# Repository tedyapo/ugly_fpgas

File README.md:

# ugly_fpgas
Breakout PCBs for ugly-style prototyping with small FPGAs

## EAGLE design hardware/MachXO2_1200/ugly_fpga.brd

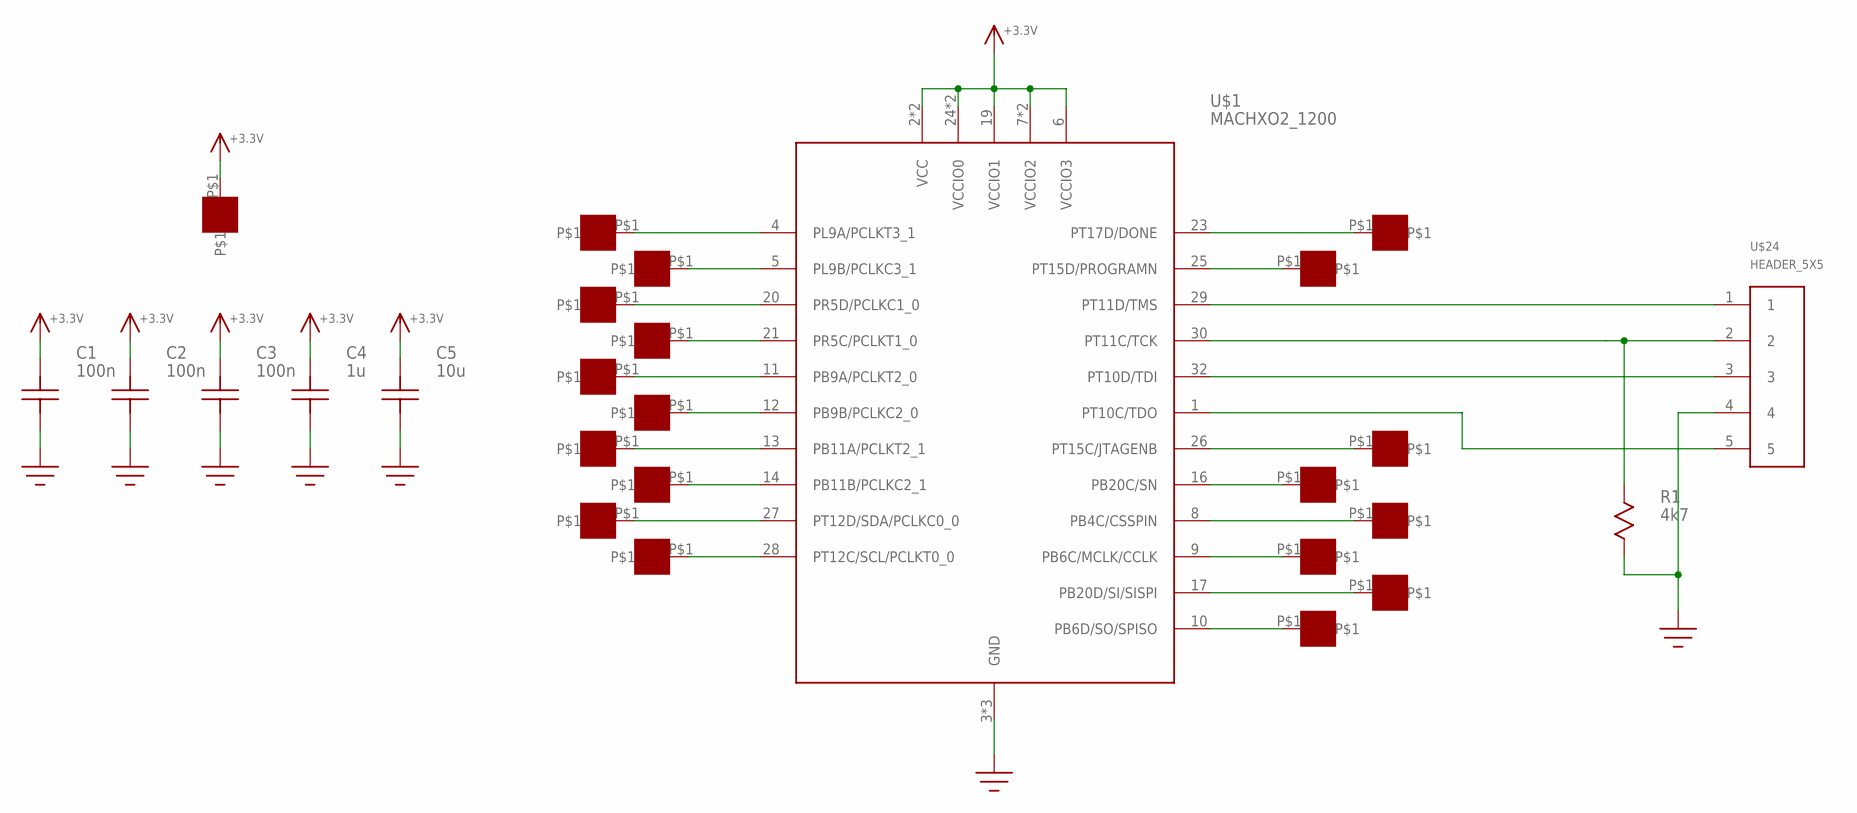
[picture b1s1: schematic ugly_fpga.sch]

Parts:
C1, C2, C3: 100n; C0603
C4: 1u; C0603
C5: 10u; C0603
R1: 4k7; R0603
U$1: MACHXO2_1200; QFN32_5X5
U$6, U$7, U$8, U$9, U$10, U$11, U$12, U$13, U$14, U$15, U$16, U$17, U$18, U$19, U$20, U$21, U$22, U$23, U$30: PAD50MIL; PAD_50MIL
U$24: HEADER_5X5; HEADER_SMT_1X5

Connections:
+3.3V: C1.P$2, C2.P$2, C3.P$2, C4.P$2, C5.P$2, U$1.2 (VCC), U$1.6 (VCCIO3), U$1.7 (VCCIO2), U$1.15 (VCCIO2), U$1.18 (VCC), U$1.19 (VCCIO1), U$1.24 (VCCIO0), U$1.31 (VCCIO0), U$30.P$1
GND: C1.P$1, C2.P$1, C3.P$1, C4.P$1, C5.P$1, R1.P$2, U$1.3 (GND), U$1.22 (GND), U$1.PAD (GND), U$24.4
unnamed: U$1.4 (PL9A/PCLKT3_1), U$6.P$1
unnamed: U$1.5 (PL9B/PCLKC3_1), U$7.P$1
unnamed: U$1.20 (PR5D/PCLKC1_0), U$8.P$1
unnamed: U$1.21 (PR5C/PCLKT1_0), U$9.P$1
unnamed: U$1.11 (PB9A/PCLKT2_0), U$10.P$1
unnamed: U$1.12 (PB9B/PCLKC2_0), U$11.P$1
unnamed: U$1.13 (PB11A/PCLKT2_1), U$12.P$1
unnamed: U$1.14 (PB11B/PCLKC2_1), U$13.P$1
unnamed: U$1.27 (PT12D/SDA/PCLKC0_0), U$14.P$1
unnamed: U$1.28 (PT12C/SCL/PCLKT0_0), U$15.P$1
unnamed: U$1.23 (PT17D/DONE), U$22.P$1
unnamed: U$1.25 (PT15D/PROGRAMN), U$23.P$1
unnamed: U$1.26 (PT15C/JTAGENB), U$21.P$1
unnamed: U$1.16 (PB20C/SN), U$20.P$1
unnamed: U$1.8 (PB4C/CSSPIN), U$19.P$1
unnamed: U$1.9 (PB6C/MCLK/CCLK), U$18.P$1
unnamed: U$1.17 (PB20D/SI/SISPI), U$17.P$1
unnamed: U$1.10 (PB6D/SO/SPISO), U$16.P$1
unnamed: U$1.29 (PT11D/TMS), U$24.1
unnamed: R1.P$1, U$1.30 (PT11C/TCK), U$24.2
unnamed: U$1.32 (PT10D/TDI), U$24.3
unnamed: U$1.1 (PT10C/TDO), U$24.5

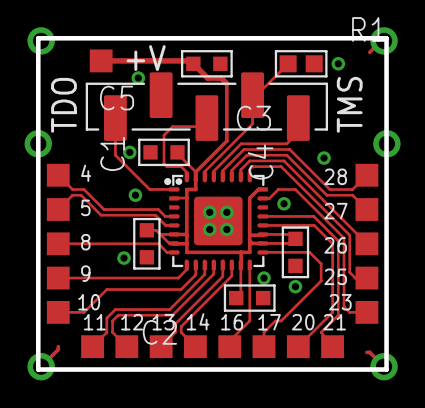
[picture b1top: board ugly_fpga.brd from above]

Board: 2 copper layers, 19.3 x 18.4 mm, 27 parts (0 on the bottom side), 24 nets.

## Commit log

2018-03-01 first PCB design
